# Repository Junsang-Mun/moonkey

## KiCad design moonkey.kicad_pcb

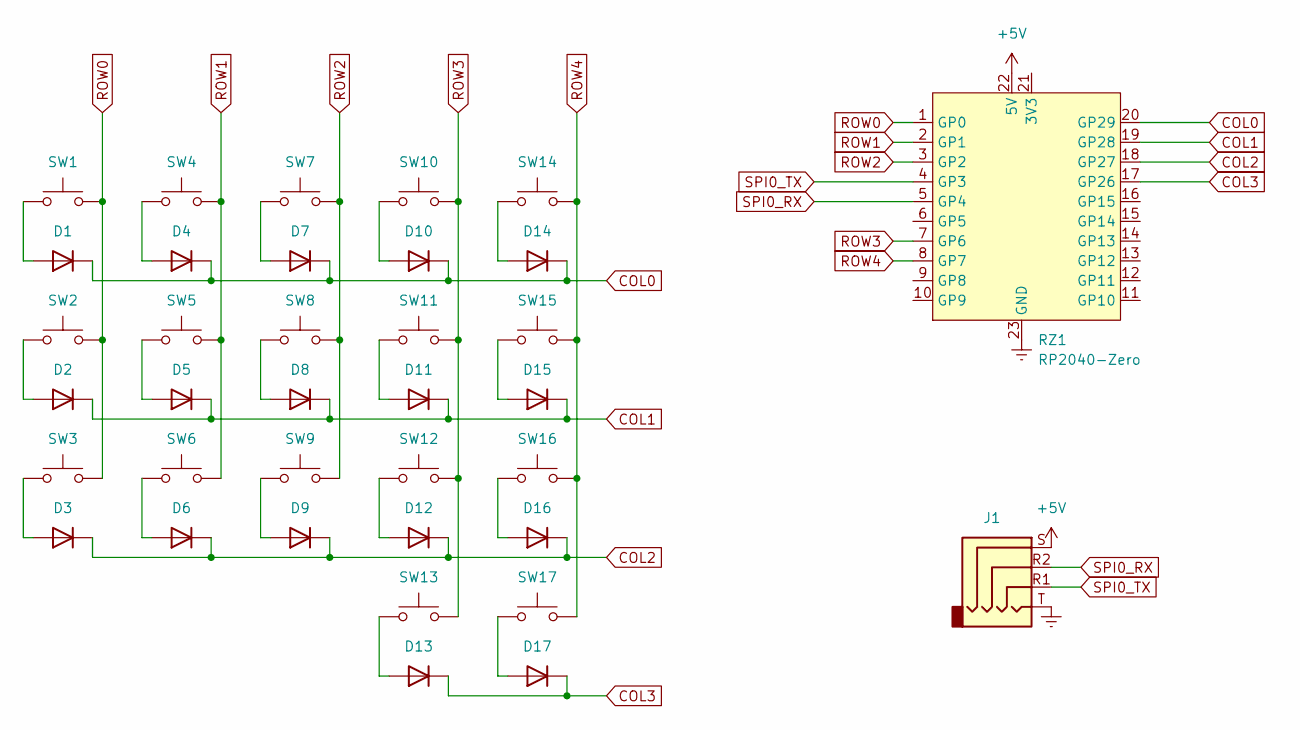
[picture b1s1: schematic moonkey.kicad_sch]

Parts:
D1, D2, D3, D4, D5, D6, D7, D8, D9, D10, D11, D12, D13, D14, D15, D16, D17: 1N4148; D_DO-35_SOD27_P7.62mm_Horizontal
J1: AudioJack4; PJ320D_rev
RZ1: RP2040-Zero; RP2040
SW1, SW2, SW3, SW4, SW5, SW6, SW7, SW8, SW9, SW10, SW11, SW12, SW13, SW14, SW15, SW16, SW17: SW_Push; Cherry_1u_rev

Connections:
+5V: J1.S, RZ1.22 (5V)
COL0: D1.1 (K), D4.1 (K), D7.1 (K), D10.1 (K), D14.1 (K), RZ1.20 (GP29)
COL1: D2.1 (K), D5.1 (K), D8.1 (K), D11.1 (K), D15.1 (K), RZ1.19 (GP28)
COL2: D3.1 (K), D6.1 (K), D9.1 (K), D12.1 (K), D16.1 (K), RZ1.18 (GP27)
COL3: D13.1 (K), D17.1 (K), RZ1.17 (GP26)
Earth: J1.T, RZ1.23 (GND)
unnamed: D1.2 (A), SW1.1
unnamed: D2.2 (A), SW2.1
unnamed: D3.2 (A), SW3.1
unnamed: D4.2 (A), SW4.1
unnamed: D5.2 (A), SW5.1
unnamed: D6.2 (A), SW6.1
unnamed: D7.2 (A), SW7.1
unnamed: D8.2 (A), SW8.1
unnamed: D9.2 (A), SW9.1
unnamed: D10.2 (A), SW10.1
unnamed: D11.2 (A), SW11.1
unnamed: D12.2 (A), SW12.1
unnamed: D13.2 (A), SW13.1
unnamed: D14.2 (A), SW14.1
unnamed: D15.2 (A), SW15.1
unnamed: D16.2 (A), SW16.1
unnamed: D17.2 (A), SW17.1
ROW0: RZ1.1 (GP0), SW1.2, SW2.2, SW3.2
ROW1: RZ1.2 (GP1), SW4.2, SW5.2, SW6.2
ROW2: RZ1.3 (GP2), SW7.2, SW8.2, SW9.2
ROW3: RZ1.7 (GP6), SW10.2, SW11.2, SW12.2, SW13.2
ROW4: RZ1.8 (GP7), SW14.2, SW15.2, SW16.2, SW17.2
SPI0_RX: J1.R2, RZ1.5 (GP4)
SPI0_TX: J1.R1, RZ1.4 (GP3)

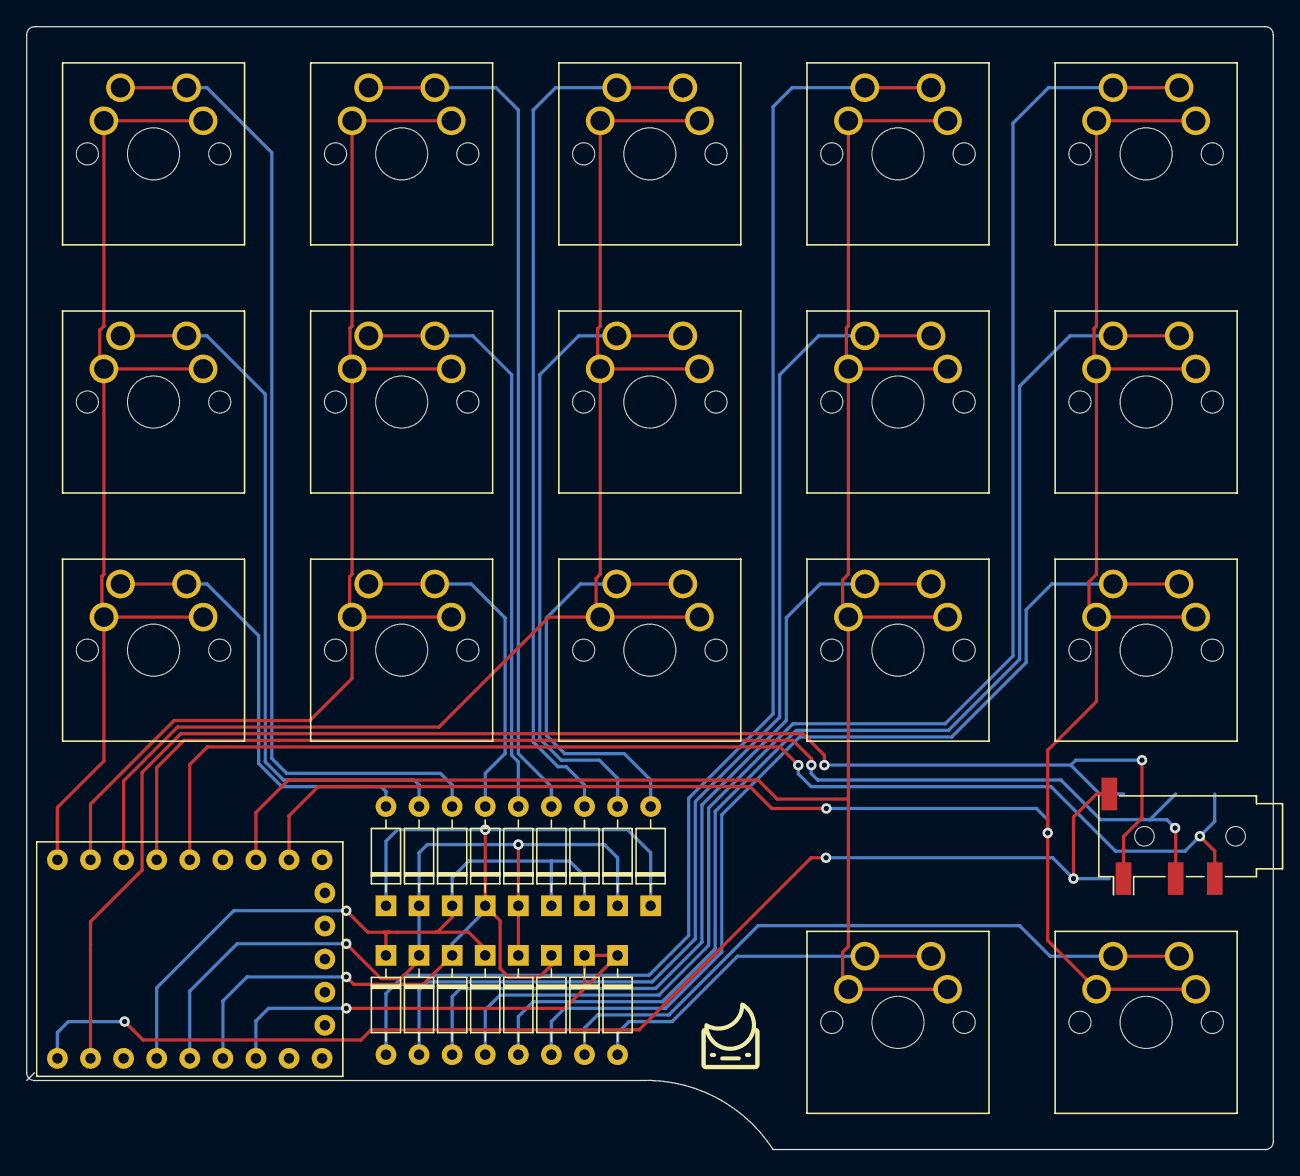
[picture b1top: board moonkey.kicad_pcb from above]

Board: 2 copper layers, 95.7 x 86.2 mm, 36 parts (1 on the bottom side), 30 nets.

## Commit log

2022-12-08 [init] repository init
2022-12-09 update gitignore
2022-12-10 keyboard layout chagned, scheme update(pins change)
2022-12-15 uptate: ortholinear
